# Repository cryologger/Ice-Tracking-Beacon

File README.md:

# Cryologger - Iceberg Tracking Beacon (ITB)

### Note: This project is under active development. 

## 1.0 Introduction
Icebergs and ice islands represent significant hazards to marine navigation and offshore infrastructure at a time when demand for access to Canada’s Arctic waters is increasing. There is a growing demand for in situ iceberg tracking data to monitor their drift trajectory and improve predictions of ice hazard occurrence and behaviour, yet the high cost of commercial tracking devices often prevents monitoring at optimal spatial and temporal resolutions.

The Cryologger Ice Tracking Beacon (ITB), built using inexpensive, open-source hardware and software, provides a reliable and cost-effective platform for monitoring the drift of icebergs and ice islands in the Canadian Arctic.

## 2.0 Methods

### 2.1 Design

The Cryologger ITB is based on the open-source Arduino platform (www.arduino.cc) and built using low-cost, do-it-yourself electronics that can be easily modified to meet the needs of the end-user. Code was written using the Arduino Integrated Development Environment (IDE) and benefits from the availability of community-generated libraries.

Planned for extended deployments in harsh Arctic conditions, the Cryologger ITB provides long-term measurements of GNSS position, temperature, pressure, pitch, roll, tilt-compensated heading and battery voltage. Data are transmitted over the Iridium satellite network at specified intervals and can be remotely updated based on the desired sampling frequency. Collected data are made available in near-real time at https://cryologger.org.

#### 2.1.1 Design Iterations

More information about the design of versions 1.0 and 2.0 of the Cryologger ITB can be found in the following publication:

[Garbo, A., & Mueller, D. (2024). Cryologger Ice Tracking Beacon: A Low-Cost, Open-Source Platform for Tracking Icebergs and Ice Islands. _Sensors_, _24_(4), Article 4. https://doi.org/10.3390/s24041044](https://www.mdpi.com/1424-8220/24/4/1044)

Version 3.0 of the Cryologger ITB builds on the successes of previous versions and features a number of improvements to the design, including:
* 3.3 V power is now provided directly from a Pololu 3.3 V step-down voltage regulator, bypassing the Feather M0's onboard AP2112 LDO regulator (-55 μA).
* A dedicated 5 V step-down voltage regulator was added to power the RockBLOCK Iridium transceiver.
* The DS3231 real-time clock (RTC) was removed in favour of the SAMD21's internal RTC for all timekeeping and alarm functionality with periodic time synchronizations with the GPS.
* The LSM303 accelerometer/magnetometer was replaced with the LSM6DS33 + LIS3MDL IMU due to the sensor reaching its end-of-life (EOL).
* The temperature/pressure and IMU sensors are now powered directly through SAMD21 GPIO pins, allowing for power to be completely removed during sleep.
* A 10MΩ + 1 MΩ resistor divider is now used to measure the battery voltage (+2.4 μA).

A major change in v3.0 is a custom carrier board PCB that is designed to greatly simplify the assembly process. The PCB was designed in KiCad and fabricated by JLCPCB. 

<p align="center"><b>Figure 1:</b> 3D rendering of Cryologger iceberg drift tracking beacon carrier board designed in KiCad.</p>

#### 2.1.2 Bill of Materials (BOM)

**Table 1.** Bill of materials and associated costs for components used in the Cryologger ITB v3.1. Prices are listed in USD and are current as of December 2023. Taxes and shipping not included. <sup>1</sup>Denotes optional component. Please note BOM is a work in progress.
| Component | Product | Quantity | Cost (USD) |
| --- | --- | :---: | :---: |
| PCB | [Custom Cryologger Printed Circuit Board](https://jlcpcb.com) | 1 | $5.00 | 
| Satellite transceiver | [Rock7 RockBLOCK 9603](https://www.groundcontrol.com/us/product/rockblock-9603-compact-plug-and-play-satellite-transmitter/) | 1 | $267.50 |
| Satellite antenna<sup>1</sup> | [Maxtena M1621HCT-P-SMA](https://maxtena.com/products/f-passive/m1621hct-p-sma-iridium-passive-antenna/) | 1 | $54.00 |
| Microcontroller | [Adafruit Feather M0 Basic Proto](https://www.adafruit.com/product/2772) | 1 | $19.95 |
| GNSS Receiver | [Adafruit Ultimate GPS FeatherWing](https://www.adafruit.com/product/3133) | 1 | $24.95 |
| IMU | [Adafruit LSM303AGR Accelerometer Magnetometer](https://www.adafruit.com/product/4413) | 1 | $12.50 |
| Sensor | [Adafruit BME280 Temperature Humidity Pressure Sensor](https://www.adafruit.com/product/2652) | 1 | $14.95 |
| Voltage regulator | [Pololu D36V6F3 3.3V 600mA Step-Down Voltage Regulator](https://www.pololu.com/product/3791) | 1 | $6.95 |
| Voltage regulator | [Pololu D36V6F5 5V 600mA Step-Down Voltage Regulator](https://www.pololu.com/product/3792) | 1 | $6.95 |
| Resistor | [10 M 1% 0.6 W resistor](https://www.mouser.ca/ProductDetail/594-MBB02070C1005FCT) | 1 | $0.29 |
| Resistor | [1 M 1% 0.6 W resistor](https://www.mouser.ca/ProductDetail/594-B0207C1M000F5T) | 1 | $0.20 |
| Capacitor | [0.1 uF Capacitor](https://mou.sr/481ILov) | 1 | $0.23 |
| Power connector |	[Phoenix Contact MSTB 2,5/ 2-ST-5,08 - 1757019](https://mou.sr/47HAA0B) | 1 | $0.60 |
| Power connector	| [Phoenix Contact MSTBA 2,5/ 2-G-5,08 - 1757242](https://mou.sr/3R27Ick) | 1 | $1.81 |
| Connector |	[Molex PicoBlade PCB Header](https://mou.sr/3qLrmgc) | 1| $0.55 |
| Connector |	[Molex PicoBlade Crimp Housing](https://mou.sr/3lXOY2x])| 2| $0.36 |
| Cable Assembly |	Molex PicoBlade Pre-crimped Jumper Wires | 5 | |
| Enclosure | [Nanuk 904](https://nanukcases.ca/products/nanuk-904) | 1 | $47.95 |
| Battery | [Tadiran TLP93121](https://www.tadiranbat.com/assets/tlp-93121-b-al1.pdf) | 1 | $145.50 |
| **Total** | | | |

<p align="center"><b>Figure 2:</b> Assembled Cryologger ice drift tracking beacon housed in Nanuk case and 3D-printed case lid removed.</p>

### 2.2 Operation

The programming logic of the Cryologger ITB optimizes sleep and wake cycles to minimize overall power consumption. When initially powered on, the system attempts to acquire a signal from the GNSS receiver and synchronizes the RTC with the current date and time. It then sets an alarm for the initial sampling interval and enters a low-power, deep-sleep mode. When the alarm triggers, the system wakes, records the time, and acquires a GNSS position. Next, measurements of all onboard sensors are collected (Table 2). These data are stored into memory and when the software determines the appropriate transmission interval has been met, it attempts to transmit the data using the RockBLOCK satellite transceiver. The software then disables power to all components, sets the next alarm, and returns to sleep.

#### 2.2.1 Measurements

**Table 2.** Measurements recorded and transmitted by the Cryologger ITB v3.0, including variable sizes.
|     Variable             |     Unit    |     Description                                   |     Size (bytes)    |
|--------------------------|-------------|---------------------------------------------------|---------------------|
|     unixtime             |     s       |     Unix time (seconds since 1970-01-01)          |     4               |
|     temperature_int      |     °C      |     Internal temperature                          |     2               |
|     humidity_int         |     %       |     Internal humidity                             |     2               |   
|     pressure_int         |     hPa     |     Internal pressure                             |     2               |   
|     pitch                |     °       |     Pitch angle                                   |     2               |   
|     roll                 |     °       |     Roll angle                                    |     2               |   
|     heading              |     °       |     Tilt-compensated magnetic heading (0-360°)    |     2               |   
|     latitude             |     °       |     GNSS latitude                                 |     4               |   
|     longitude            |     °       |     GNSS longitude                                |     4               |   
|     satellites           |             |     Number of GNSS satellites in view             |     2               |   
|     hdop                 |             |     GNSS horizontal dilution of precision         |     2               |   
|     voltage              |     V       |     Battery voltage                               |     2               |   
|     transmit_duration    |     s       |     Transmission time of SBD message              |     2               |   
|     transmit_status      |             |     Iridium return code                           |     1               |   
|     message_counter      |             |     Number of transmitted messages                |     2               |   

#### 2.2.2 Data Transmission and Processing

The Cryologger ITB records its position and sensor measurements nominally on an hourly basis and transmits at an interval of 3 hours. Data are transmitted via the Iridium satellite network as a Short Burst Data (SBD) message. The ITB attempts to transmit each message for up to 180 seconds, and if unsuccessful, the message is stored in a temporary buffer and reattempted at the next transmission interval. Both the sampling and transmission frequency of individual Cryologgers can be remotely modified by the end-user. Successfully transmitted SBD messages are received by an Iridium ground station and sent to Ground Control's server. These data are then forwarded to Amazon Web Services (AWS), where they are decoded using a Python script, stored in a database, and visualized on the Cryologger website: https://cryologger.org.

## 3.0 Deployments

A total of 37 Cryologger ITBs have been deployed between 2018 and 2023 (Figure 3), primarily during the annual Amundsen Expedition. Deployments are performed by helicopter from the CCGS Amundsen on icebergs and ice islands along the coasts of Ellesmere Island, Baffin Island and Greenland (Figure 3). At the time of deployment, a compass heading of the tracking beacon was recorded. Where possible, a 360° aerial photo survey of the iceberg was performed for use with Structure-from-Motion photogrammetry to create 3D models of the iceberg.

<p align="left"><b>Figure 3:</b> Map of Cryologger ice drift tracking beacons deployed between 2018 and 2023.</p>

The overall suitability of potential targets was determined by assessing the iceberg’s size, shape, and location. Where possible, icebergs selected to be instrumented with a tracking beacon were large enough to survive drifting south to the Grand Banks of Newfoundland and far enough away from the coast to increase the chances of being carried southward by the currents and avoid becoming grounded in shallow coastal areas. 

<p align="center"><b>Figure 4:</b> Examples of icebergs instrumented with Cryologger iceberg tracking beacons during the 2021 Amundsen Expedition.</p>

## 4.0 Results

The operation of the Cryologger ITBs greatly exceeded expectations, with the operational lifespans of deployments made in 2018 ranging from 310 to 1530 days, and those in 2019 ranging from 333 to 615 days. The most frequent causes of loss of communication with the ITBs was due to the eventual deterioration (calving or rolling) or catastrophic break-up of the iceberg and subsequent destruction of the beacon. In many cases, it was possible to use remote sensing imagery to observe major break-up events of icebergs that immediately resulted in transmissions from the beacon ceasing.

### 4.1 Iceberg Drift
A snapshot of iceberg drift tracks recorded from all Cryologger ITB deployments as of December 2023 is shown in Figure 4. This data can also be viewed in real-time at: https://cryologger.org/tracking

<p align="center"><b>Figure 5:</b> Map of Cryologger iceberg drift track tracks from beacons deployed between 2018 and 2023.</p>

## 5.0 Conclusion

The overall success of the Cryologger ITB has demonstrated that it can provide a robust platform for the collection of in-situ iceberg tracking data. With a total cost of approximately $700 USD in materials each, this represents a cost-effective alternative to existing proprietary commercial systems. 

The development and deployment of these novel iceberg tracking beacons were intended to enhance and supplement existing iceberg observation networks within the Canadian Arctic and data collected from the Cryologgers has already contributed to a database of iceberg tracking beacon tracks compiled by the Canadian Ice Service (CIS). Most importantly, this research demonstrates to the scientific community that inexpensive, open-source hardware and software can provide a viable solution for the monitoring of icebergs and ice island drift patterns within the Canadian Arctic and beyond!

Development of the next iteration of the Cryologger ITB is currently underway, which is focused on improving overall reliability, exploring the use of environmentally friendly materials, and improvements that will allow it to transform into an ocean drifter buoy once the breakup of the icebergs occurs. 

## Repository Contents

* **/Documentation** - Assembly, deployment and troubleshooting guides, as well as information on components used and associated costs.

* **/Hardware** - KiCad PCB schematic and design files.

* **/Software** -  Arduino code and Python data analysis scripts.

## License Information
Cryologger code, firmware, and software is licensed under the GNU General Public License v3.0 (https://www.gnu.org/licenses/gpl-3.0.en.html). 

<p xmlns:cc="http://creativecommons.org/ns#" >Cryologger hardware is licensed under <a href="https://creativecommons.org/licenses/by-nc-sa/4.0/?ref=chooser-v1" target="_blank" rel="license noopener noreferrer" style="display:inline-block;">CC BY-NC-SA 4.0 </a></p>

Cheers,

**Adam Garbo**

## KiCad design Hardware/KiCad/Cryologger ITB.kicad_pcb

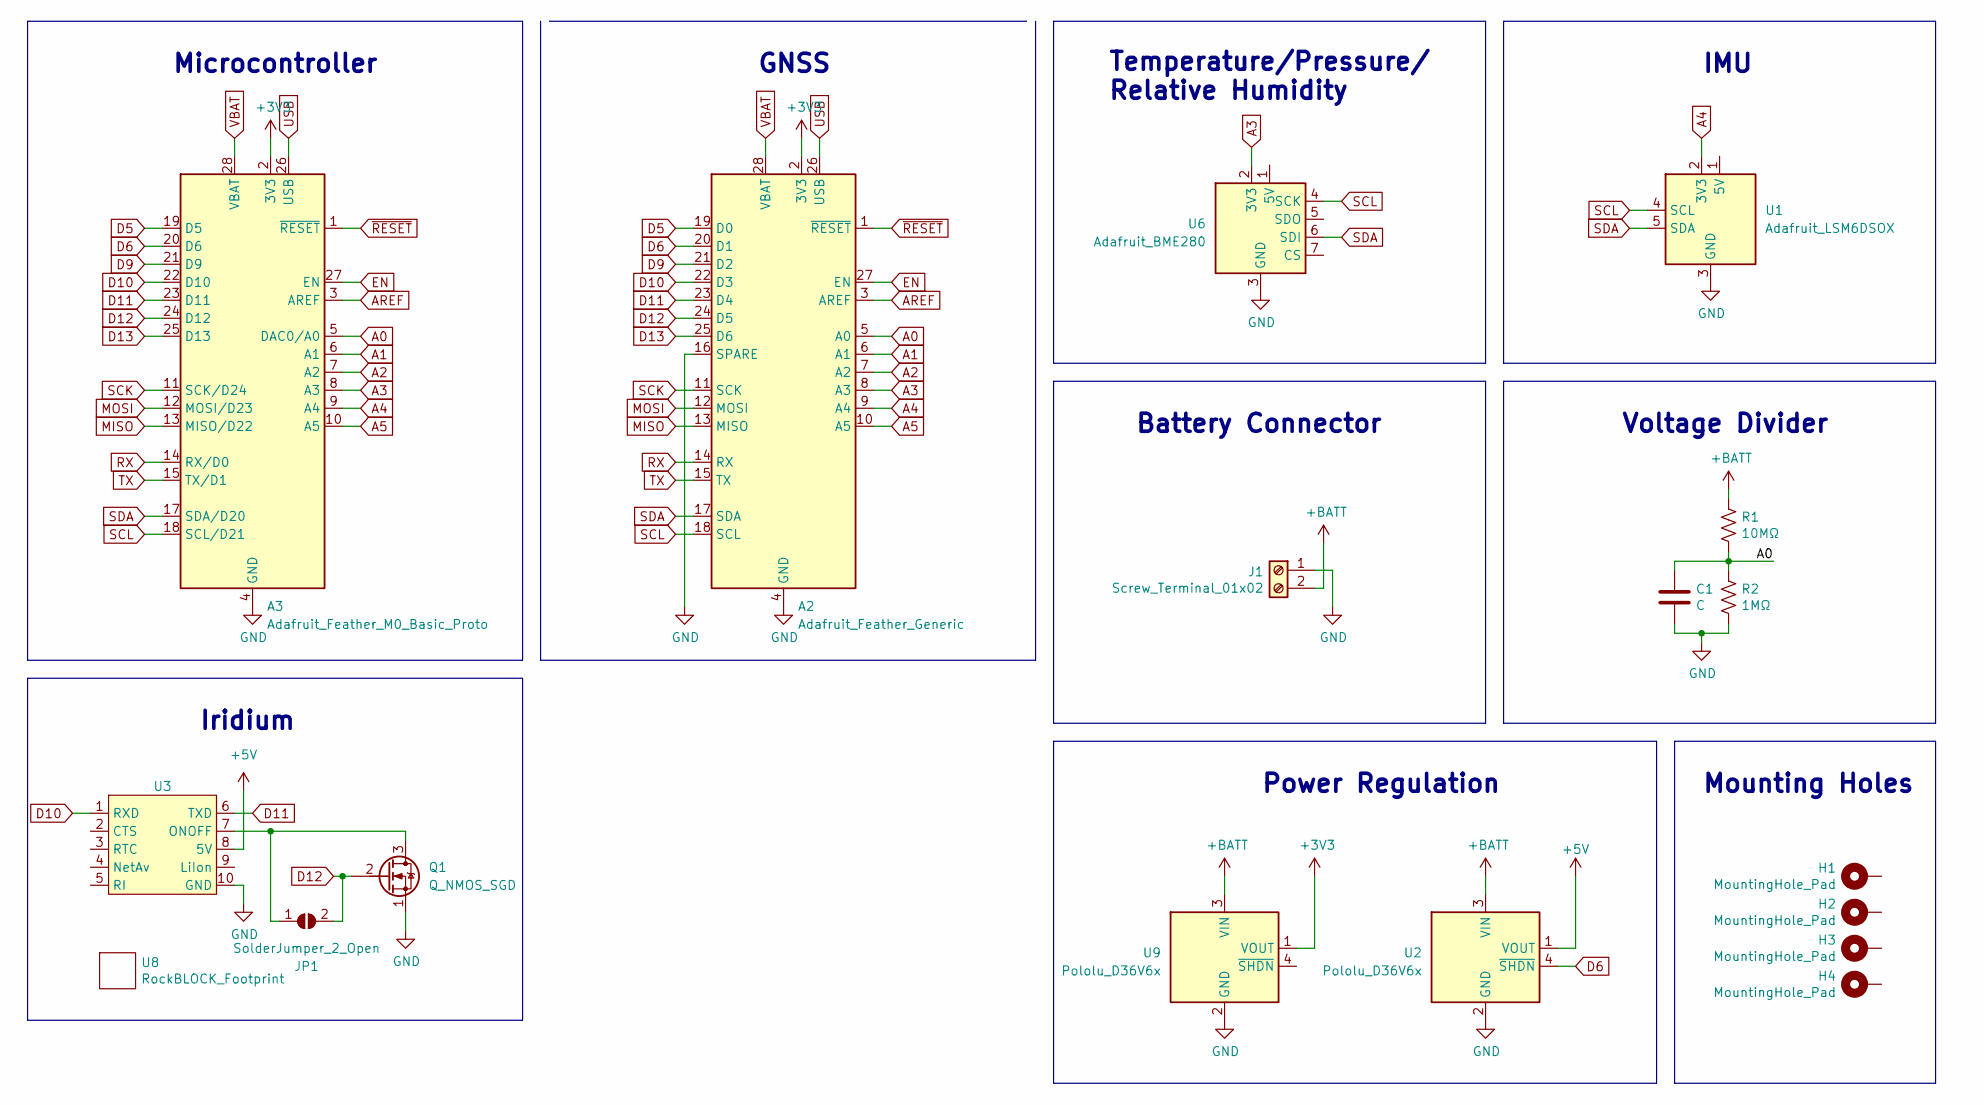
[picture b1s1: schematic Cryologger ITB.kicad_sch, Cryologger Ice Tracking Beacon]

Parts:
A2: Adafruit_Feather_Generic; Adafruit_Feather_Header_Double
A3: Adafruit_Feather_M0_Basic_Proto; Adafruit_Feather_Header_Double
C1: C; C_Disc_D3.8mm_W2.6mm_P2.50mm
H1, H2, H3, H4: MountingHole_Pad; MountingHole_3mm_Pad
J1: Screw_Terminal_01x02; PhoenixContact_MSTBA_2,5_2-G-5,08_1x02_P5.08mm_Horizontal
JP1: SolderJumper_2_Open; SolderJumper-2_P1.3mm_Open_RoundedPad1.0x1.5mm
Q1: Q_NMOS_SGD; TO-92
R1: 10MΩ; R_Axial_DIN0207_L6.3mm_D2.5mm_P10.16mm_Horizontal
R2: 1MΩ; R_Axial_DIN0207_L6.3mm_D2.5mm_P10.16mm_Horizontal
U1: Adafruit_LSM6DSOX; Adafruit_LSM6DS0X
U2, U9: Pololu_D36V6x
U3: Molex_PicoBlade_53047-1010_1x10_P1.25mm_Vertical
U6: Adafruit_BME280
U8: RockBLOCK_Footprint; RockBLOCK_9603

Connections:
+3V3: A2.2 (3V3), A3.2 (3V3), U9.1 (VOUT)
+5V: U2.1 (VOUT), U3.8 (5V)
+BATT: J1.2, R1.1, U2.3 (VIN), U9.3 (VIN)
A0: A2.5 (A0), A3.5 (DAC0/A0), C1.1, R1.2, R2.1
A1: A2.6 (A1), A3.6 (A1)
A2: A2.7 (A2), A3.7 (A2)
A3: A2.8 (A3), A3.8 (A3), U6.2 (3V3)
A4: A2.9 (A4), A3.9 (A4), U1.2 (3V3)
A5: A2.10 (A5), A3.10 (A5)
AREF: A2.3 (AREF), A3.3 (AREF)
D5: A2.19 (D0), A3.19 (D5)
D6: A2.20 (D1), A3.20 (D6), U2.4 (~SHDN)
D9: A2.21 (D2), A3.21 (D9)
D10: A2.22 (D3), A3.22 (D10), U3.1 (RXD)
D11: A2.23 (D4), A3.23 (D11), U3.6 (TXD)
D12: A2.24 (D5), A3.24 (D12), JP1.2 (B), Q1.2 (G)
D13: A2.25 (D6), A3.25 (D13)
EN: A2.27 (EN), A3.27 (EN)
GND: A2.4 (GND), A2.16 (SPARE), A3.4 (GND), A3.16 (GND), C1.2, J1.1, Q1.1 (S), R2.2, U1.3 (GND), U2.2 (GND), U3.10 (GND), U6.3 (GND), U9.2 (GND)
MISO: A2.13 (MISO), A3.13 (MISO/D22)
MOSI: A2.12 (MOSI), A3.12 (MOSI/D23)
unnamed: JP1.1 (A), Q1.3 (D), U3.7 (ONOFF)
RX: A2.14 (RX), A3.14 (RX/D0)
SCK: A2.11 (SCK), A3.11 (SCK/D24)
SCL: A2.18 (SCL), A3.18 (SCL/D21), U1.4 (SCL), U6.4 (SCK)
SDA: A2.17 (SDA), A3.17 (SDA/D20), U1.5 (SDA), U6.6 (SDI)
TX: A2.15 (TX), A3.15 (TX/D1)
USB: A2.26 (USB), A3.26 (USB)
VBAT: A2.28 (VBAT), A3.28 (VBAT)
~RESET: A2.1 (~RESET), A3.1 (~RESET)

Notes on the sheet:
Microcontroller
Power Regulation
Iridium
Mounting Holes
Battery Connector
IMU
Voltage Divider
Temperature/Pressure/ Relative Humidity
GNSS

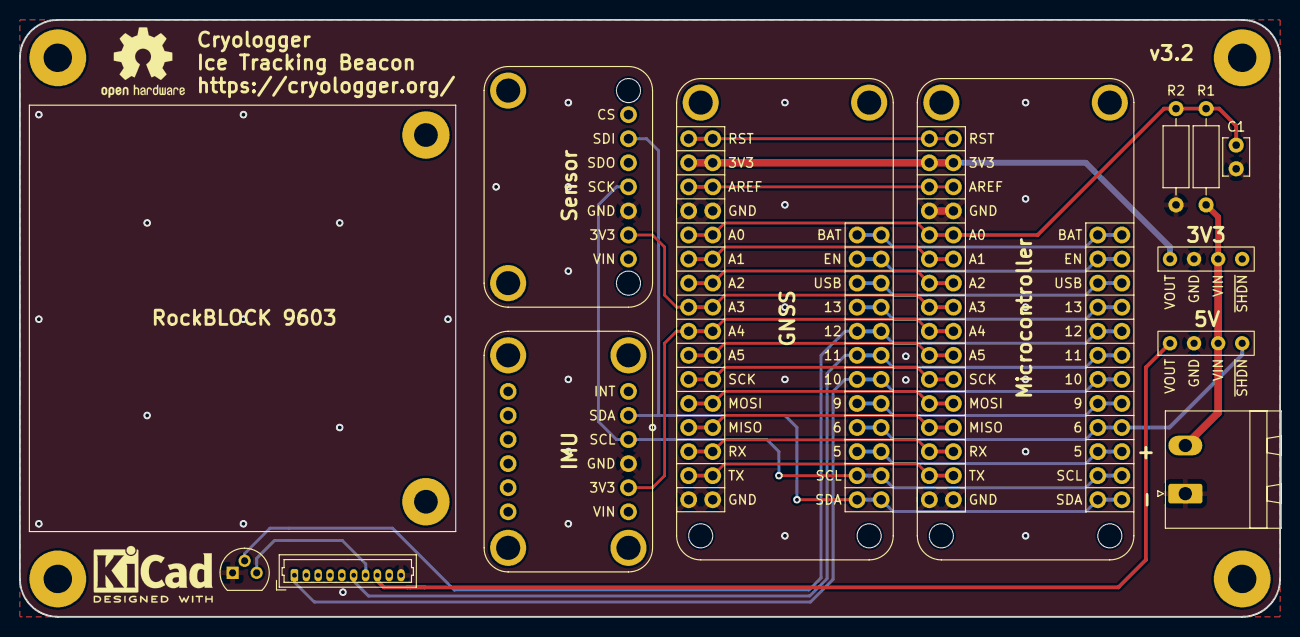
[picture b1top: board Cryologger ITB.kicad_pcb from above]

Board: 2 copper layers, 133.0 x 63.0 mm, 18 parts (1 on the bottom side), 30 nets.

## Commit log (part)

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2019-09-23 Inital Cryologger V2 update
2019-10-08 Cryologger V2 update
2020-01-12 Rename cryologger_v2.ino to amundsen_2019.ino
2020-01-12 Rename cryologger_v1.ino to amundsen_2018.ino
2020-03-18 Cryologger V3 update
2020-06-04 Create LICENSE
2020-11-02 Standardize project folders
2020-11-03 Update MicroMod code example
2020-11-09 Update MicroMod code
2020-11-11 Add Qwiic Micro code example
2020-11-14 Update MicroMod and Qwiic Micro code
2020-11-16 Update Qwiic Micro code
2020-11-17 Update Qwiic Micro code
    Add support for WS2812B RGB LED (aka NeoPixel) and ICM-20948 IMU
2020-11-18 Major update to Qwiic Micro code
    Rename tabs to allow for future additions
2020-11-23 Update Qwiic Micro code for deployment tests
    Added code to utilize RockBLOCK 9603 in addition to SparkFun Qwiic Iridium 9603N
2020-11-26 Add RTC drift calculation functionality to Qwiic Micro code
2020-12-03 Add Cryologger photos
2020-12-03 Add Cryologger deployment photos
2020-12-23 Update v1.0 documentation
    Standardize folder naming structure. Add deployment and tracjectory maps. Add photos of icebergs and beacon deployments.
2020-12-27 Remove unsupported WS2812B LED code from MicroMod
2020-12-29 Major update to Qwiic Micro code
    Add external RTC code. Switch to debug print macros. Remove all code relating to SparkX products (i.e. Qwiic Power Switch, Qwiic Iridium 9603N).
2020-12-31 Add MOSFET to Qwiic Micro to control power to peripherals
    Improve RTC alarms. Improve non-blocking blink delays. Improve power down and power up flow.
2021-01-01 Change Qwiic Micro MT-SBD message data processing to union/structures
2021-01-01 Change method of printing MT-SBD message
2021-01-02 Improve processing of MT-SBD messages
    Add a changelog file. Remove old examples.
2021-01-04 Fix MO-SBD message retransmitting
2021-01-04 Minor updates for prototype testing
2021-01-06 Update to MicroMod code
2021-01-06 Minor MicroMod updates
2021-01-07 MicroMod prototype testing changes
2021-01-09 Add delay to sensor readings
2021-01-15 MicroMod prototype code updates
2021-01-19 MicroMod code updates
2021-01-31 Change approach of synchronizing real-time clock
2021-01-31 Minor update to RTC synchronization code
2021-01-31 Reinstate firstTimeFlag functionality for Qwiic Micro code
2021-01-31 Qwiic Micro troubleshooting updates
2021-02-01 Reinstate firstTimeFlag for MicroMod code
2021-02-02 Switch to new u-blox library callbacks instead of polling
2021-02-16 Update MicroMod code for deployment tests
2021-02-20 Add Qwiic Iridium 9603N functionality to Qwiic Micro code
2021-03-02 Change Qwiic Micro code to use FastLED library
2021-04-10 Switch to transmitting data via RockBLOCK
2021-04-14 Add power control functions
2021-04-16 Add Adafruit version of code
2021-04-16 Update low power test code
2021-04-19 Major update
2021-04-20 Modify WDT code to use GCLK1
2021-04-22 Major update
    Feed RTC-configured GCLK2 to WDT. Rework processing of MT-SBD messages. Standardize SBD variable names. Rework functions to print MO/MT-SBD messages. Revert to iterationCounter variable name.
2021-04-26 Change to LSM6DS33 + LIS3MDL
2021-05-05 Minor updates
2021-05-06 Enable GPS altitude measurement
2021-05-12 Add altitude measurement
2021-05-12 Remove RGB LED code
2021-05-15 Update IMU code
    Switch to Adafruit LSM6DS33/LIS3MDL libraries and Jim Remington's improved approach to pitch, roll and tilt-compensated heading calculations
2021-05-16 Update tilt-compensation example
2021-05-16 Minor update
2021-05-22 Upload Gerber files
2021-05-25 Switch to DPS310 temperature/pressure sensor
2021-05-25 Prototype testing modifications
2021-05-25 Update analog pin for battery measurements
2021-05-28 Update ADC configuration code
2021-05-28 Decrease ADC sampling time length
2021-05-30 Remove altitude measurement
2021-06-02 Add KiCad files
2021-06-16 Remove prototype code
2021-07-27 Add IMU calibration data
2021-08-01 Add 3D-printed mounting STL files
2021-09-06 Fix GPS synchronization bug
    Improve failure counter checks and adjust RTC alarm increase values. Prepare code for version 3.2 release.
2021-09-12 Add photos
2021-11-26 Update cryologger_itb_adafruit.ino
    Add library versions.
2022-04-02 Rename files
    Add memory leak bug fix comment.
2022-04-10 Make use of Iridium startup timeout option
2022-04-14 Update bill of materials
2022-05-31 Major update
    Rename tabs. Add dedicated ADC code tab. Simplify RTC alarm failure logic. Change all references of GPS to GNSS.
2022-05-31 Update KiCad files
2022-06-01 Improve GNSS validity checks for RTC sync
2022-06-01 Update battery voltage measurement to 10/1 MOhm resistor divider
    Make two measurements to ensure correct reading.
2022-06-01 Change RTC alarms to daily
2022-06-01 Minor updates to prepare for system testing
2022-06-01 Rename file
2022-06-07 Finalize deployment code for 2022 Milne Fiord deployments
2022-10-20 Add statistics tab
2022-10-20 Merge IMU with sensors tab
    Add code support for BME280 and LSM303AGR sensors. Rename functions to be specific to the sensor.
2022-10-20 Add ADC calibration and float mapping functionality
2022-10-22 Add LSM303AGR min/max calibration code
2022-10-22 Change voltage divider calculation
    Standardized code with Cryologger AWS repository.
2022-10-23 Code commenting and cleaning
    Standardized WDT code.
2022-12-04 Change IMU support to LSM303AGR
2022-12-04 Remove GNSS configuration commands
2022-12-04 Minor updates
    Updated code to LMS303AGR accelerometer/magnetometer. Improved program flow.
2022-12-15 Change initial alarm from daily to hourly
2023-01-22 Remove DPS310 code and rename alarmInterval to sampleInterval
    Continued work on standardizing AWS and ITB code (i.e., functions, logic, etc.). Added battery voltage cutoff alarm. Changed sample interval to minutes.
2023-01-22 Standardize loop program logic
    Moved transmission logic to main loop. Added sample counter.
2023-03-05 Major changes to KiCad design files
    Updated design to v3.1. Began standardization of Cryologger designs to metric measurements. Redid schematic using Cryologger library symbols and footprints. Generated new Gerber design files. Generat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
2023-03-05 Reorganized software files
    Created new Arduino folder to store firmware and test code.
2023-04-04 Prepare code for deployment
2023-04-04 Add 3D printing G-Code
2023-04-04 Minor updates to PCB design
2023-04-16 Adjust timings
    Reverted GNSS timeout to seconds.
2023-04-16 Minor updates
    Fixed location of sleep code. Rearranged order of when sensors are powered up. Converted library links to open Arduino IDE Library Manager.
2023-04-17 Update MT-SBD union structure and associated code
2023-04-17 Print correct RTC alarm
2023-04-22 Improve setSleepPin function
2023-05-06 Configure code for test unit
2023-06-28 Update SAMD board definition version
2023-07-04 Standardize size of sampleInterval in struct/union
2023-09-04 Upload documentation images
2023-09-04 Revert documentation to legacy Arduino IDE
2023-09-04 Rename images
2023-09-04 Correct file extension
2023-09-04 Upload images
2023-10-21 Fix maximum sample interval
2023-10-21 Update version
    Removed magnetometer calibration deployment values.
2023-12-05 Remove G-Code
2023-12-07 Update tilt compensation code
2024-01-12 Include additional license information
2024-01-17 Add DOI badge
2024-02-15 Add link to publication
2024-02-15 Fix typo
2024-03-14 Remove deprecated symbols file
2024-05-03 Add N-MOSFET to PCB to control RockBLOCK v3.F
    Updated KiCad files. Added Creative Commons license.
2024-06-08 Fix typos
2024-06-28 Change function to return value
2024-06-28 Add flag for RockBLOCK v3.F pin configuration
    Improved code comments. Improved Serial Monitor output. Updated libraries.
2024-10-26 Remove Python code
2025-02-16 Remove outdated Gerber files
2025-03-30 Remove unused tabs
2025-03-30 Improve code commenting
    Renamed tabs. Adopted Clang 14.0.0 formatting. Simplified `myDelay` function. Changed `blinkLed` to default to LED_BUILTIN.
2025-03-31 Separate IMU code
    Improved code commenting.
2025-03-31 Improve code commenting
    Added new function to display sensor measurements.
2025-03-31 Change MT-SBD validation code
    Removed battery cutoff variable and restored alarm interval variable.
2025-03-31 Make epoch variables global
    Improved code commenting.
2025-03-31 Major updates
    Adopted Clang 14.0.0 formatting. Improved code commenting. Rearrange variable groupings. Added new user configuration section. Largely reverted main loop logic to v3.0.0 without battery cutoff.
2025-04-09 Improve code comments
2025-06-17 Improve GNSS fix validity check
2025-06-18 Create GNSS configuration function and reimplement charsSeen variable
2025-06-18 Replace unixtime-based alarms with explicit minute, hourly and daily alarms
2025-06-18 Improve code commenting
2025-06-18 Major updates
    Reorganized structure of code, emphasizing user configuration. Incorporated new explicit RTC alarms. Reorganized and renamed variables to improve clarity.
2025-06-22 Add function to print unixtime timestamp
2025-06-22 Minor changes to handle GNSS data
2025-06-22 Improve code comments
    Improved. Iridium error message function.
2025-07-17 Create case_v3.2.stl
    Added hole for micro-USB connector.
2025-08-09 Improve code commenting and debug messages
2025-08-26 Development of ring buffer transmission functionality
2025-08-28 Continue development of ring buffer transmission functionality
2025-08-28 Major updates to IMU functionality
    Added 3×3 calibration, inverse soft-iron matrix. Calibration values now loaded from static .h file.
2025-08-28 Move code sections to separate .h files
    Moved Iridium union/structure to structs.h and IMU calibration values to imu_calibration.h.
2025-08-30 Add IMU calibration code
    Added code to collect raw magnetometer data, a Python script to perform an ellipsoid fit and code to test implementation.
2025-08-30 Add IMU calibration values
2025-08-30 Clean code comments and formatting
2025-09-04 Update IMU calibration values
2025-09-05 Update output filename
2025-09-10 Fix alarm bug causing minute drift
    Changed alarm method to be based on epoch time. Switched to breakTime to handle leap year logic.
2025-09-11 Change to fixed-width integer types
2025-09-11 Improve GNSS acquisition logic
    Added thresholds for minimum signal quality based on HDOP and satellite number with best acquired fallback.
2025-09-11 Cleanup to streamline repository
2025-09-11 Update badges
2026-05-07 Remove power control from within IMU functions
2026-05-07 Adopt GNSS component median approach
2026-05-07 Minor updates
    Improved RockBLOCK hardware version logic. Added GNSS time guards. Updated firmware and library versions.
2026-05-09 Improve handing of MO/MT message sizing
2026-05-09 Minor updates
    Improved SBD data by casting variables to avoid overflows. Updated unique identifier.
2026-05-09 Improve GNSS/RTC sync functionality
    Moved function from GNSS to RTC tab. Capped daily alarm at 1 day.
2026-05-18 Improve floating point math
2026-05-18 Add local variable
2026-05-18 Make structs consistent
2026-05-18 Add no data sentinels
2026-05-19 Improve sensor functionality
    Added reattempts to initialization, no-data sentinels, and constrained variables.
2026-05-19 Improved floating point math
2026-05-19 Improve code commenting and debugging
    Improved code efficiency. Removed redundant variables.
2026-05-19 Add additional fix gate variable
    Standardized early return functions.
2026-05-19 Simplify Iridium transmission code
    Simplified ring buffer. Testing to be conducted.
2026-05-19 Improve code comments and efficiency
    Added no-data sentinels to IMU. Removed redundant variables declared in RTC.
2026-05-24 Make RockBLOCK sleep control compatible with v3.D and below
2026-05-24 Correct pin peripheral order
2026-05-28 Correct SBD size
2026-06-23 Add missing SBD size definition
2026-06-28 Use DEBUG_WRITE macro for GNSS char echo
    Changed to prevent DEBUG gate from being bypassed.

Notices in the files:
Hardware/KiCad/Cryologger ITB.kicad_pcb:
© 2024. This work is openly licensed via CC BY-NC-SA 4.0.
